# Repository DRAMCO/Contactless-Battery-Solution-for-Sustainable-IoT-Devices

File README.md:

# Contactless Battery Solution for Sustainable IoT Devices: Assessment of Environmental Impact

Supplementary material for "MDPI Electronics special issue Wireless Power Transfer Systems: Design and Implementation"

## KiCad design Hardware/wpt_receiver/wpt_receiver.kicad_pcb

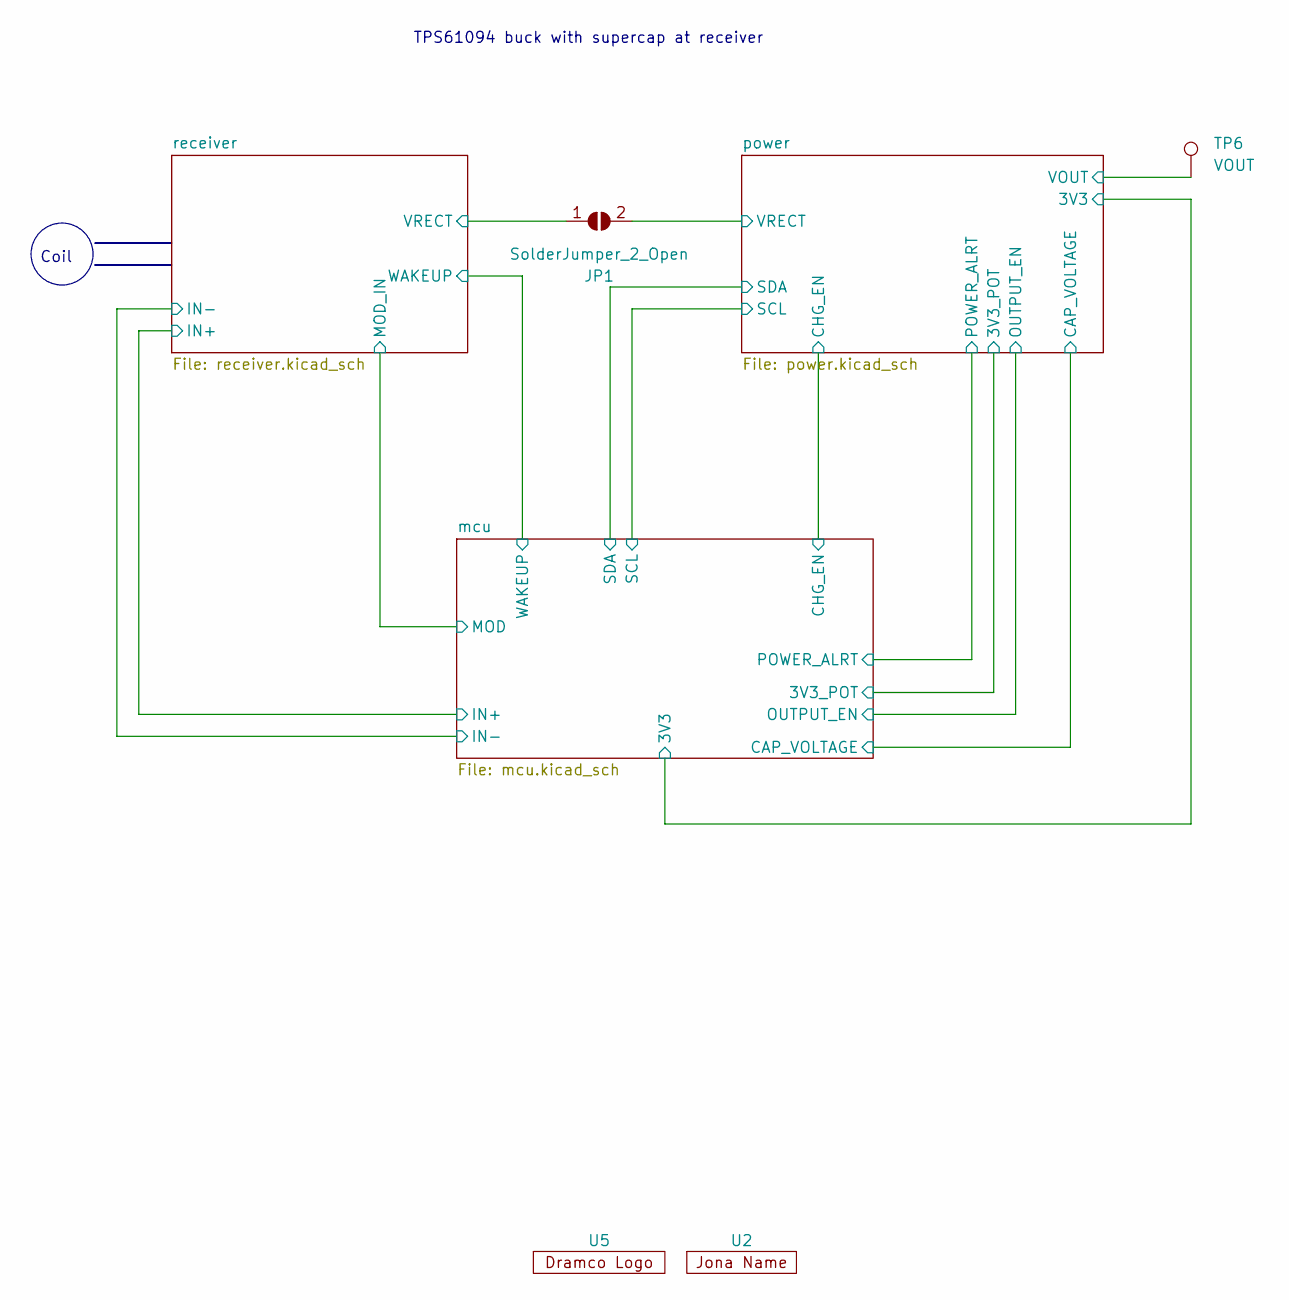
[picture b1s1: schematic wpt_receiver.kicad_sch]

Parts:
JP1: SolderJumper_2_Open; SolderJumper-2_P1.3mm_Open_RoundedPad1.0x1.5mm
TP6: VOUT; TestPoint_THTPad_2.5x2.5mm_Drill1.2mm
U2: Jona Name
U5: dramco_logo_small

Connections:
/power/VOUT: TP6.1; also elsewhere on the board
unnamed 32: JP1.1 (A); also elsewhere on the board
unnamed 33: JP1.2 (B); also elsewhere on the board

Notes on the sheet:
Coil
TPS61094 buck with supercap at receiver

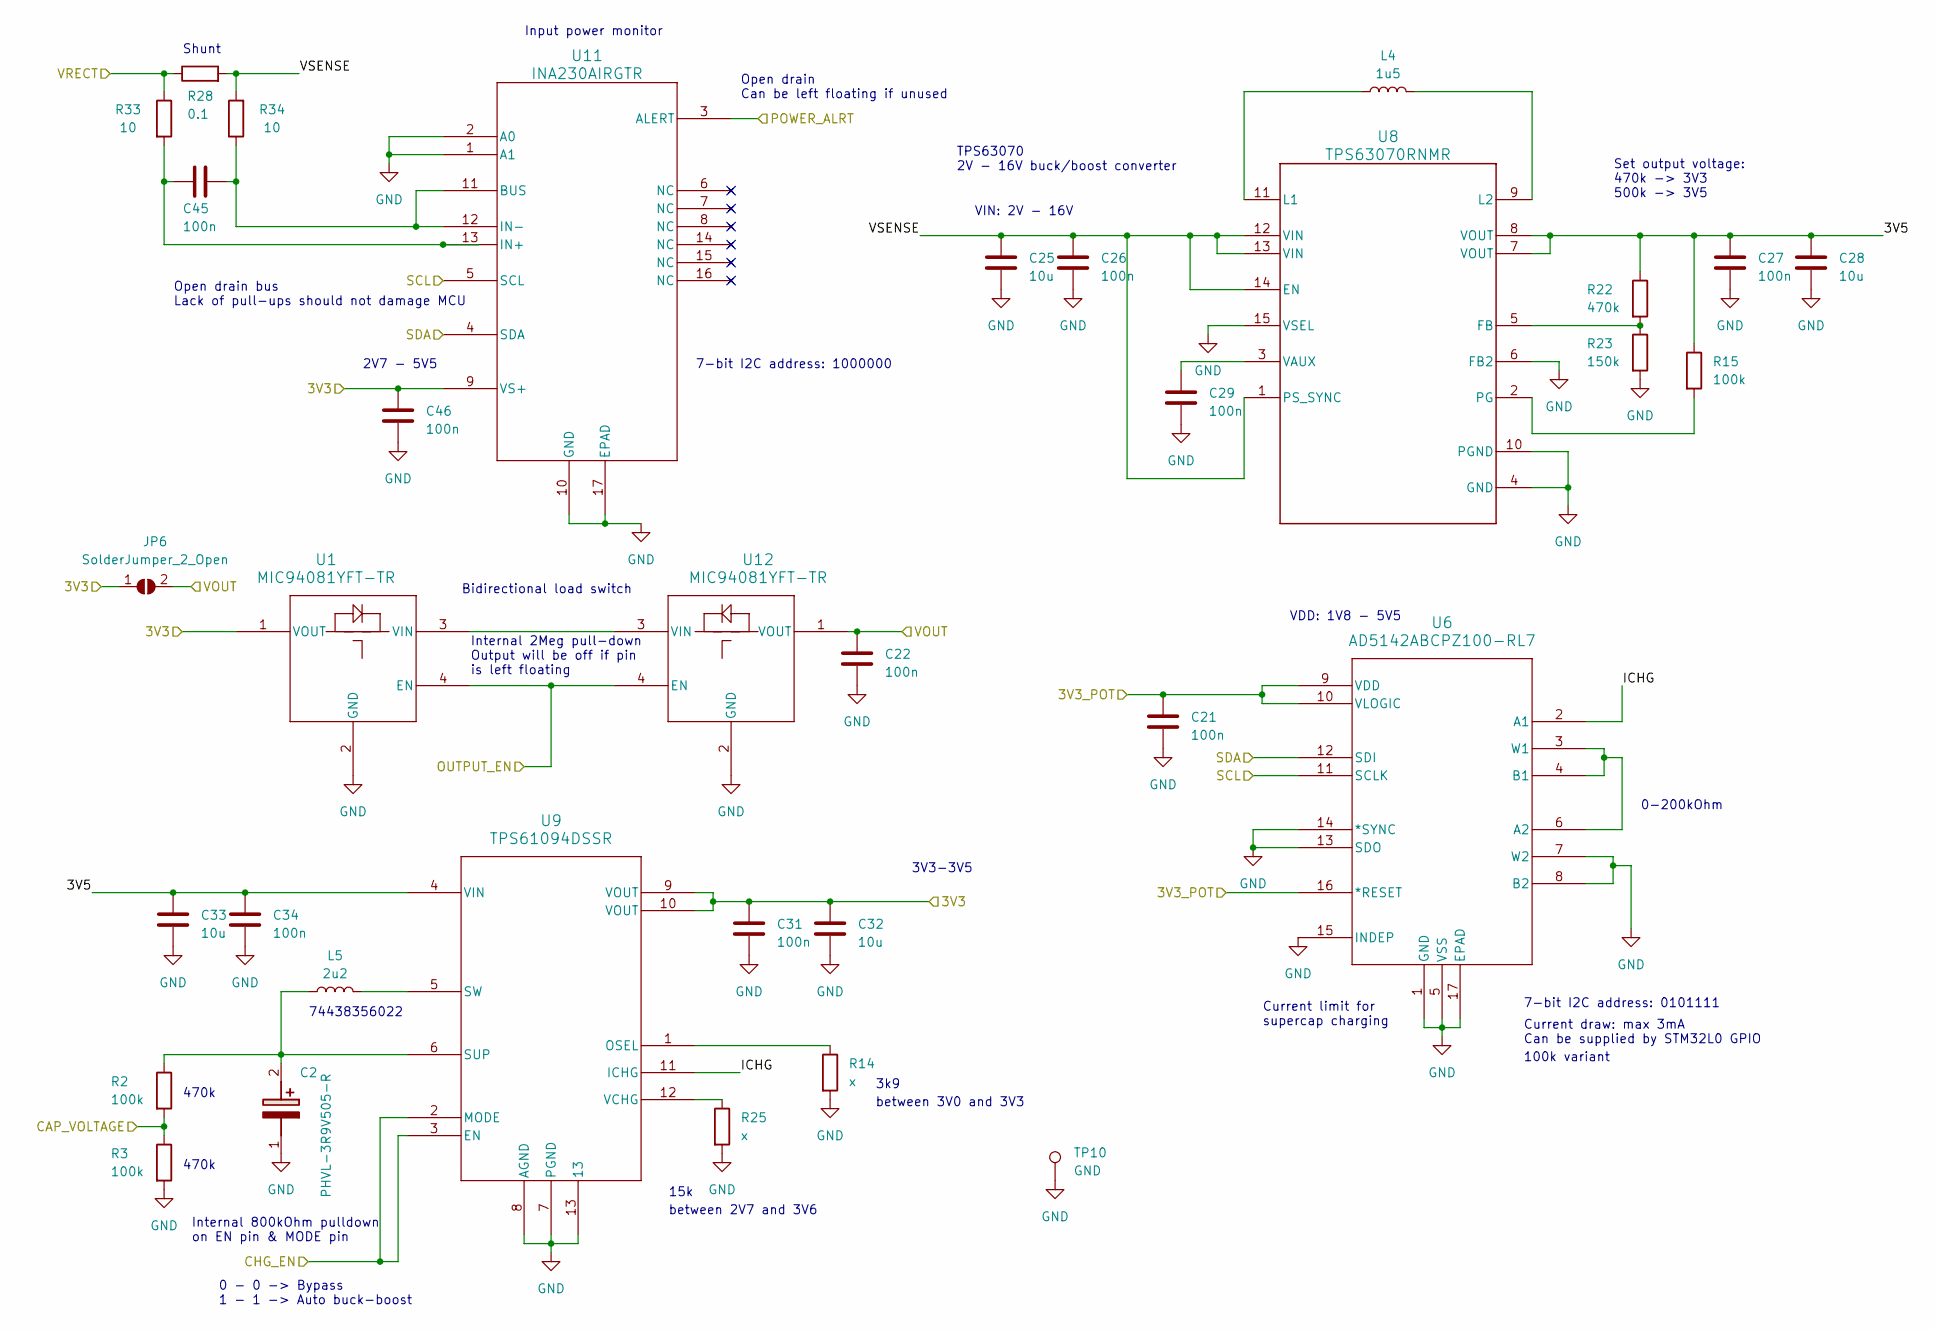
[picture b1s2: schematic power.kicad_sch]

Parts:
C2: PHVL-3R9V505-R; PHVL3R9V505R; Mouser Part Number 504-PHVL-3R9V505-R
C21, C22, C26, C27, C29, C31, C34, C45, C46: 100n; C_0603_1608Metric_Pad1.08x0.95mm_HandSolder
C25, C28, C32, C33: 10u; C_0603_1608Metric_Pad1.08x0.95mm_HandSolder
JP6: SolderJumper_2_Open; SolderJumper-2_P1.3mm_Open_RoundedPad1.0x1.5mm
L4: 1u5; L_Coilcraft_XxL4020
L5: 2u2; WE-MAPI_4020
R2, R3, R15: 100k; R_0603_1608Metric_Pad0.98x0.95mm_HandSolder
R14, R25: x; R_0603_1608Metric_Pad0.98x0.95mm_HandSolder
R22: 470k; R_0603_1608Metric_Pad0.98x0.95mm_HandSolder
R23: 150k; R_0603_1608Metric_Pad0.98x0.95mm_HandSolder
R28: 0.1; R_1206_3216Metric_Pad1.30x1.75mm_HandSolder
R33, R34: 10; R_0603_1608Metric_Pad0.98x0.95mm_HandSolder
TP10: GND; TestPoint_THTPad_2.5x2.5mm_Drill1.2mm
U1, U12: MIC94081YFT-TR; FTDFN085085-4LD-PL-1_MCH
U6: AD5142ABCPZ100-RL7; CP_16_22_ADI
U8: TPS63070RNMR; RNM0015A
U9: TPS61094DSSR; WSON_94DSSR_TEX
U11: INA230AIRGTR; RGT16_1P7X1P7

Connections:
/mcu/3V3: C31.1, C32.1, C46.1, JP6.1 (A), U1.1 (VOUT), U9.9 (VOUT), U9.10 (VOUT), U11.9 (VS+); also elsewhere on the board
/mcu/3V3_POT: C21.2, U6.9 (VDD), U6.10 (VLOGIC), U6.16 (*RESET); also elsewhere on the board
/mcu/CAP_VOLTAGE: R2.2, R3.1; also elsewhere on the board
/mcu/CHG_EN: U9.2 (MODE), U9.3 (EN); also elsewhere on the board
/mcu/OUTPUT_EN: U1.4 (EN), U12.4 (EN); also elsewhere on the board
/mcu/POWER_ALRT: U11.3 (ALERT); also elsewhere on the board
/mcu/SCL: U6.11 (SCLK), U11.5 (SCL); also elsewhere on the board
/mcu/SDA: U6.12 (SDI), U11.4 (SDA); also elsewhere on the board
/power/3V5: C27.1, C28.1, C33.1, C34.1, R15.1, R22.1, U8.7 (VOUT), U8.8 (VOUT), U9.4 (VIN)
/power/ICHG: U6.2 (A1), U9.11 (ICHG)
/power/VOUT: C22.1, JP6.2 (B), U12.1 (VOUT); also elsewhere on the board
/power/VRECT: R28.1, R33.1; also elsewhere on the board
/power/VSENSE: C25.1, C26.1, R28.2, R34.2, U8.1 (PS_SYNC), U8.12 (VIN), U8.13 (VIN), U8.14 (EN)
GND: C2.1 (-), C21.1, C22.2, C25.2, C26.2, C27.2, C28.2, C29.2, C31.2, C32.2, C33.2, C34.2, C46.2, R3.2, R14.2, R23.2, R25.2, TP10.1, U1.2 (GND), U6.1 (GND), U6.5 (VSS), U6.7 (W2), U6.8 (B2), U6.13 (SDO), U6.14 (*SYNC), U6.15 (INDEP), U6.17 (EPAD), U8.4 (GND), U8.6 (FB2), U8.10 (PGND), U8.15 (VSEL), U9.7 (PGND), U9.8 (AGND), U9.13, U11.1 (A1), U11.2 (A0), U11.10 (GND), U11.17 (EPAD), U12.2 (GND); also elsewhere on the board
unnamed: C2.2 (+), L5.1, R2.1, U9.6 (SUP)
unnamed: U1.3 (VIN), U12.3 (VIN)
unnamed: U6.3 (W1), U6.4 (B1), U6.6 (A2)
unnamed: R22.2, R23.1, U8.5 (FB)
unnamed: L4.1, U8.11 (L1)
unnamed: L4.2, U8.9 (L2)
unnamed: R15.2, U8.2 (PG)
unnamed: C29.1, U8.3 (VAUX)
unnamed: R14.1, U9.1 (OSEL)
unnamed: L5.2, U9.5 (SW)
unnamed: R25.1, U9.12 (VCHG)
unnamed: C45.1, R34.1, U11.11 (BUS), U11.12 (IN-)
unnamed: C45.2, R33.2, U11.13 (IN+)

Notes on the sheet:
7-bit I2C address: 0101111
between 2V7 and 3V6
0-200kOhm
15k
Internal 2Meg pull-down Output will be off if pin is left floating
3k9
Bidirectional load switch
Current draw: max 3mA Can be supplied by STM32L0 GPIO
VIN: 2V - 16V
between 3V0 and 3V3
Input power monitor
Set output voltage: 470k -> 3V3 500k -> 3V5
Open drain Can be left floating if unused
470k
Internal 800kOhm pulldown on EN pin & MODE pin
74438356022
Shunt
TPS63070 2V - 16V buck/boost converter
VDD: 1V8 - 5V5
Current limit for supercap charging
Open drain bus Lack of pull-ups should not damage MCU
0 - 0 -> Bypass 1 - 1 -> Auto buck-boost
2V7 - 5V5
3V3-3V5
100k variant
7-bit I2C address: 1000000

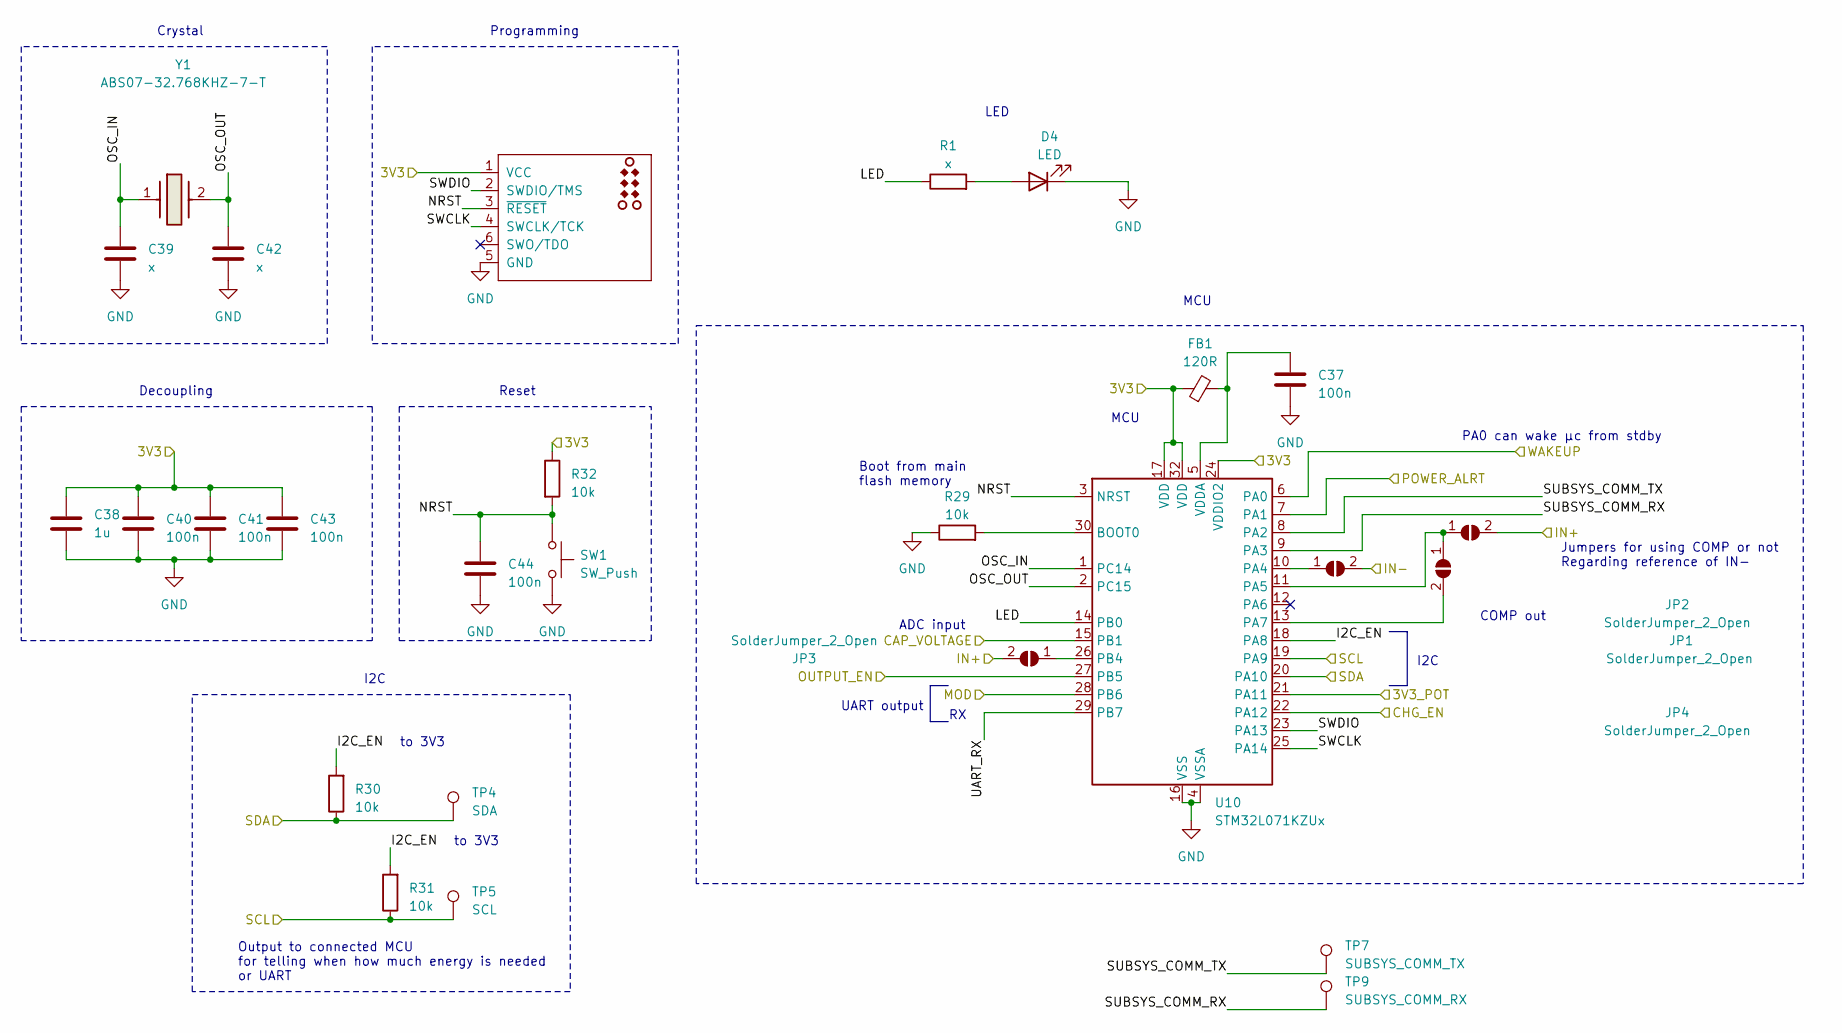
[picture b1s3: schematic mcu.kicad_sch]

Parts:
C37, C40, C41, C43, C44: 100n; C_0603_1608Metric_Pad1.08x0.95mm_HandSolder
C38: 1u; C_0603_1608Metric_Pad1.08x0.95mm_HandSolder
C39, C42: x; C_0603_1608Metric_Pad1.08x0.95mm_HandSolder
D4: LED; LED_0805_2012Metric_Pad1.15x1.40mm_HandSolder
FB1: 120R; C_0603_1608Metric_Pad1.08x0.95mm_HandSolder
J1: TC2030_SWD-MCP-NL; Tag-Connect_TC2030-IDC-NL_2x03_P1.27mm_Vertical
JP1, JP2, JP3, JP4: SolderJumper_2_Open; SolderJumper-2_P1.3mm_Open_RoundedPad1.0x1.5mm
R1: x; R_0603_1608Metric_Pad0.98x0.95mm_HandSolder
R29, R30, R31, R32: 10k; R_0603_1608Metric_Pad0.98x0.95mm_HandSolder
SW1: SW_Push; SW_Push_1P1T_NO_CK_KMR2
TP4: SDA; TestPoint_THTPad_2.5x2.5mm_Drill1.2mm
TP5: SCL; TestPoint_THTPad_2.5x2.5mm_Drill1.2mm
TP7: SUBSYS_COMM_TX; TestPoint_THTPad_2.5x2.5mm_Drill1.2mm
TP9: SUBSYS_COMM_RX; TestPoint_THTPad_2.5x2.5mm_Drill1.2mm
U10: STM32L071KZUx; QFN-32-1EP_5x5mm_P0.5mm_EP3.45x3.45mm
Y1: ABS07-32.768KHZ-7-T; ABS07; Mouser Part Number 815-ABS07-32.768K7T

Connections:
/mcu/3V3: C38.1, C40.1, C41.1, C43.1, FB1.1, J1.1 (VCC), R32.1, U10.17 (VDD), U10.24 (VDDIO2), U10.32 (VDD); also elsewhere on the board
/mcu/3V3_POT: U10.21 (PA11); also elsewhere on the board
/mcu/CAP_VOLTAGE: U10.15 (PB1); also elsewhere on the board
/mcu/CHG_EN: U10.22 (PA12); also elsewhere on the board
/mcu/I2C_EN: R30.2, R31.2, U10.18 (PA8)
/mcu/IN+: JP2.2 (B), JP3.2 (B); also elsewhere on the board
/mcu/LED: R1.1, U10.14 (PB0)
/mcu/MOD: U10.28 (PB6); also elsewhere on the board
/mcu/NRST: C44.1, J1.3 (~RESET), R32.2, SW1.1, U10.3 (NRST)
/mcu/OSC_IN: C39.1, U10.1 (PC14), Y1.1
/mcu/OSC_OUT: C42.1, U10.2 (PC15), Y1.2
/mcu/OUTPUT_EN: U10.27 (PB5); also elsewhere on the board
/mcu/POWER_ALRT: U10.7 (PA1); also elsewhere on the board
/mcu/SCL: R31.1, TP5.1, U10.19 (PA9); also elsewhere on the board
/mcu/SDA: R30.1, TP4.1, U10.20 (PA10); also elsewhere on the board
/mcu/SUBSYS_COMM_RX: TP9.1, U10.9 (PA3)
/mcu/SUBSYS_COMM_TX: TP7.1, U10.8 (PA2)
/mcu/SWCLK: J1.4 (SWCLK/TCK), U10.25 (PA14)
/mcu/SWDIO: J1.2 (SWDIO/TMS), U10.23 (PA13)
/mcu/UART_RX: U10.29 (PB7)
/mcu/WAKEUP: U10.6 (PA0); also elsewhere on the board
/receiver/COIL-: JP4.2 (B); also elsewhere on the board
GND: C37.2, C38.2, C39.2, C40.2, C41.2, C42.2, C43.2, C44.2, D4.1 (K), J1.5 (GND), R29.1, SW1.2, U10.4 (VSSA), U10.16 (VSS), U10.31 (VSS), U10.33 (VSS); also elsewhere on the board
unnamed: D4.2 (A), R1.2
unnamed: JP1.1 (A), JP2.1 (A), U10.11 (PA5)
unnamed: JP1.2 (B), U10.13 (PA7)
unnamed: JP3.1 (A), U10.26 (PB4)
unnamed: JP4.1 (A), U10.10 (PA4)
unnamed: R29.2, U10.30 (BOOT0)
unnamed: C37.1, FB1.2, U10.5 (VDDA)

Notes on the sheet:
I2C
Crystal
MCU
PA0 can wake µc from stdby
ADC input
Decoupling
Programming
Jumpers for using COMP or not Regarding reference of IN-
to 3V3
Reset
Boot from main flash memory
Output to connected MCU for telling when how much energy is needed or UART
LED
COMP out
UART output

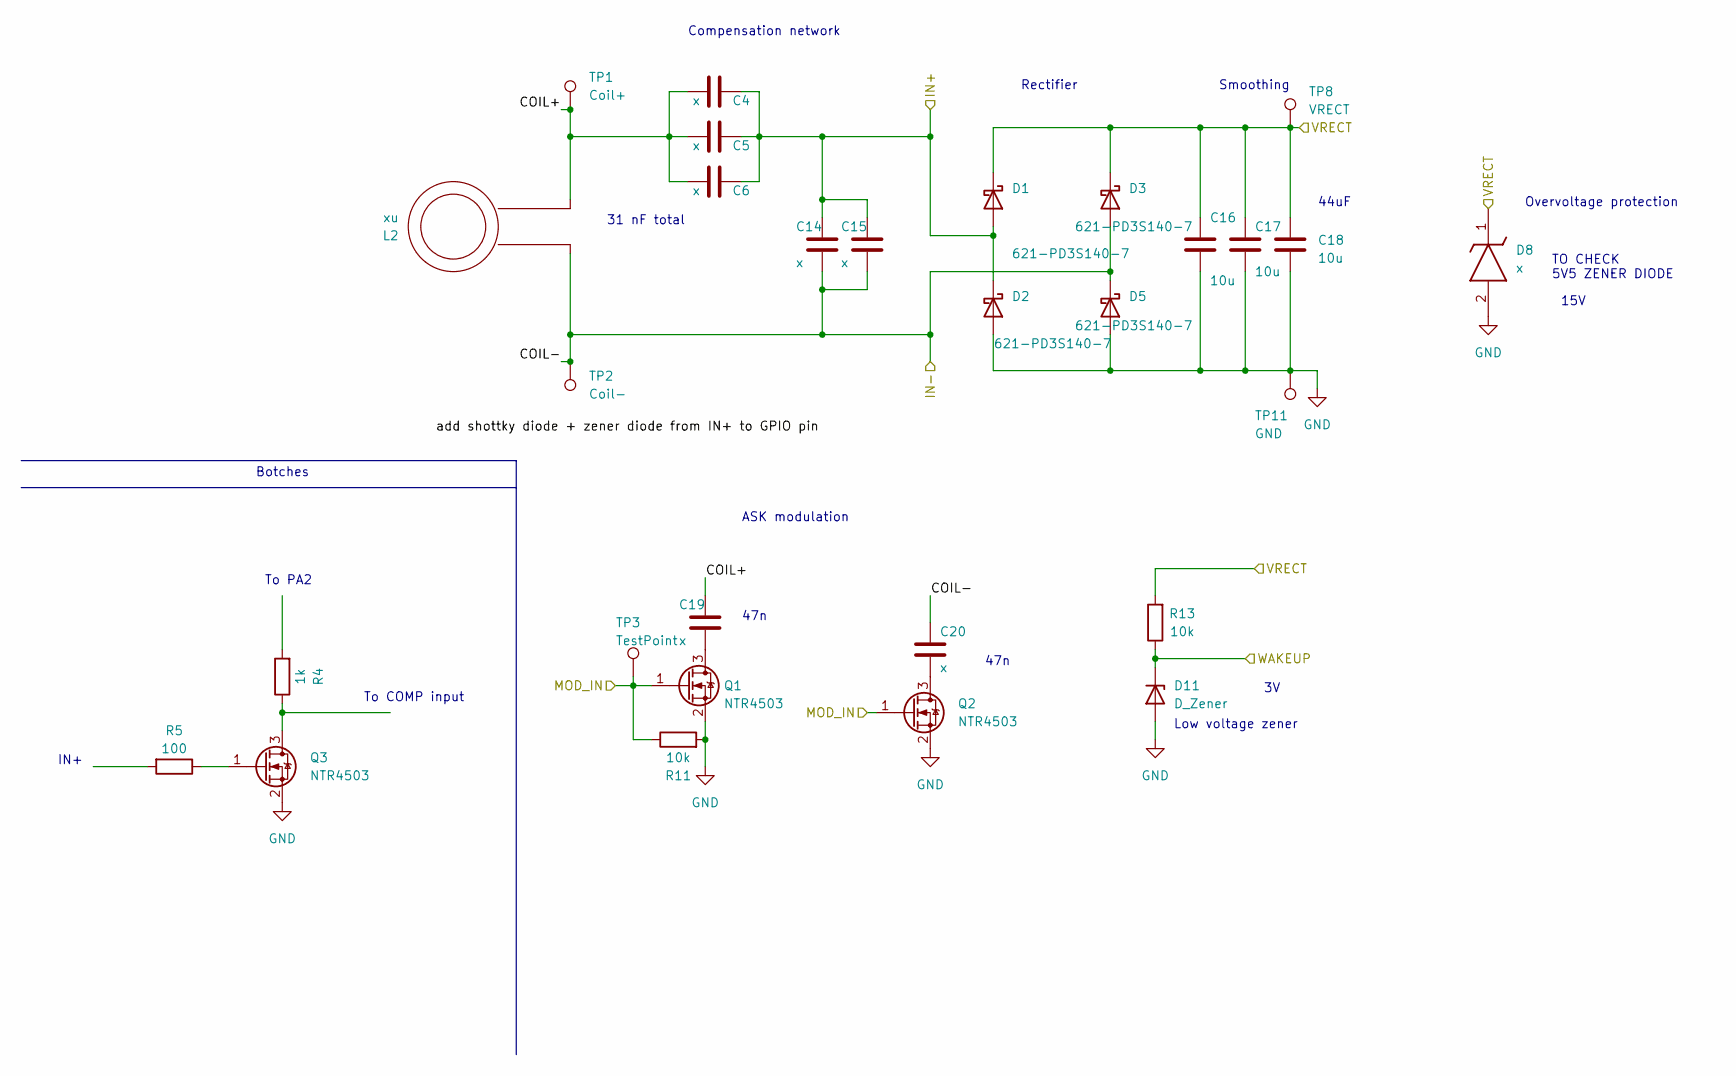
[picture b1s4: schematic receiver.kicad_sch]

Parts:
C4, C5, C6, C14, C15: x; C_0805_2012Metric_Pad1.18x1.45mm_HandSolder
C16, C17, C18: 10u; C_0603_1608Metric_Pad1.08x0.95mm_HandSolder
C19, C20: x; C_0603_1608Metric_Pad1.08x0.95mm_HandSolder
D1, D2, D3, D5: 621-PD3S140-7; D_SOD-323_HandSoldering
D8: x; D_SOD-323_HandSoldering; Mouser Part Number 621-D24V0S1U2TQ-7
D11: D_Zener; D_SOD-523
L2: xu; Wurth Coil Connector
Q1, Q2, Q3: NTR4503; SOT-23
R4: 1k; R_0603_1608Metric_Pad0.98x0.95mm_HandSolder
R5: 100; R_0603_1608Metric_Pad0.98x0.95mm_HandSolder
R11, R13: 10k; R_0603_1608Metric_Pad0.98x0.95mm_HandSolder
TP1: Coil+; TestPoint_THTPad_2.5x2.5mm_Drill1.2mm
TP2: Coil-; TestPoint_THTPad_2.5x2.5mm_Drill1.2mm
TP3: TestPoint; TestPoint_Pad_2.5x2.5mm
TP8: VRECT; TestPoint_THTPad_2.5x2.5mm_Drill1.2mm
TP11: GND; TestPoint_THTPad_2.5x2.5mm_Drill1.2mm

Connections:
/mcu/IN+: C4.2, C5.2, C6.2, C14.1, C15.1, D1.2 (A), D2.1 (K); also elsewhere on the board
/mcu/MOD: Q1.1 (G), Q2.1 (G), R11.1, TP3.1; also elsewhere on the board
/mcu/WAKEUP: D11.1 (K), R13.1; also elsewhere on the board
/receiver/COIL+: C4.1, C5.1, C6.1, C19.1, L2.2, TP1.1
/receiver/COIL-: C14.2, C15.2, C20.1, D3.2 (A), D5.1 (K), L2.1, TP2.1; also elsewhere on the board
/receiver/VRECT: C16.1, C17.1, C18.1, D1.1 (K), D3.1 (K), D8.1 (K), R13.2, TP8.1; also elsewhere on the board
GND: C16.2, C17.2, C18.2, D2.2 (A), D5.2 (A), D8.2 (A), D11.2 (A), Q1.2 (S), Q2.2 (S), Q3.2 (S), R11.2, TP11.1; also elsewhere on the board
unnamed: C19.2, Q1.3 (D)
unnamed: C20.2, Q2.3 (D)
unnamed: Q3.1 (G), R5.1
unnamed: Q3.3 (D), R4.1

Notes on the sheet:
Botches
47n
31 nF total
To COMP input
Low voltage zener
ASK modulation
IN+
Overvoltage protection
Rectifier
Compensation network
To PA2
15V
44uF
Smoothing
TO CHECK 5V5 ZENER DIODE

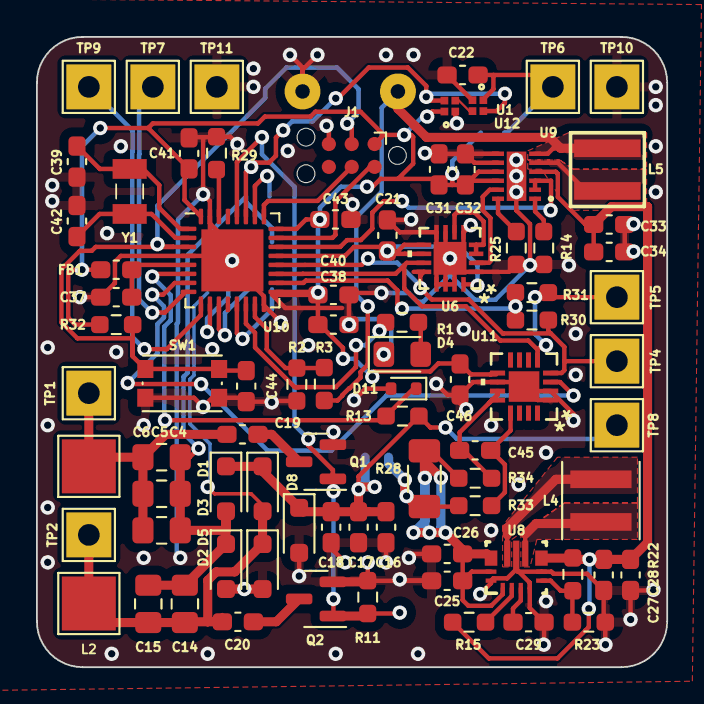
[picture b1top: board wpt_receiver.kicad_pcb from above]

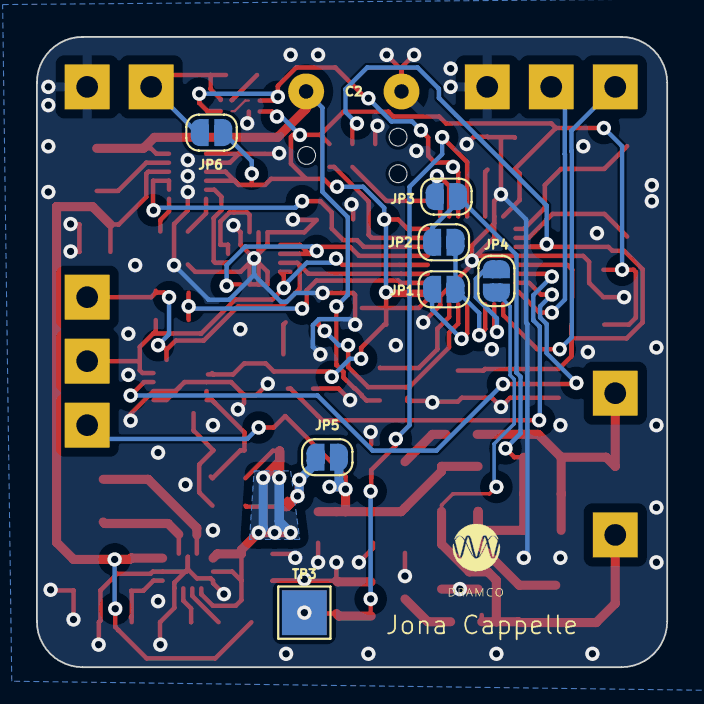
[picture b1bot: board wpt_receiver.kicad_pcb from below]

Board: 2 copper layers, 35.0 x 35.0 mm, 91 parts (9 on the bottom side), 51 nets.

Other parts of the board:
JP5: SolderJumper_2_Open; SolderJumper-2_P1.3mm_Open_RoundedPad1.0x1.5mm
U4: dramco_logo_small

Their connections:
/power/VRECT: JP5.2 (B); also elsewhere on the board
/receiver/VRECT: JP5.1 (A); also elsewhere on the board

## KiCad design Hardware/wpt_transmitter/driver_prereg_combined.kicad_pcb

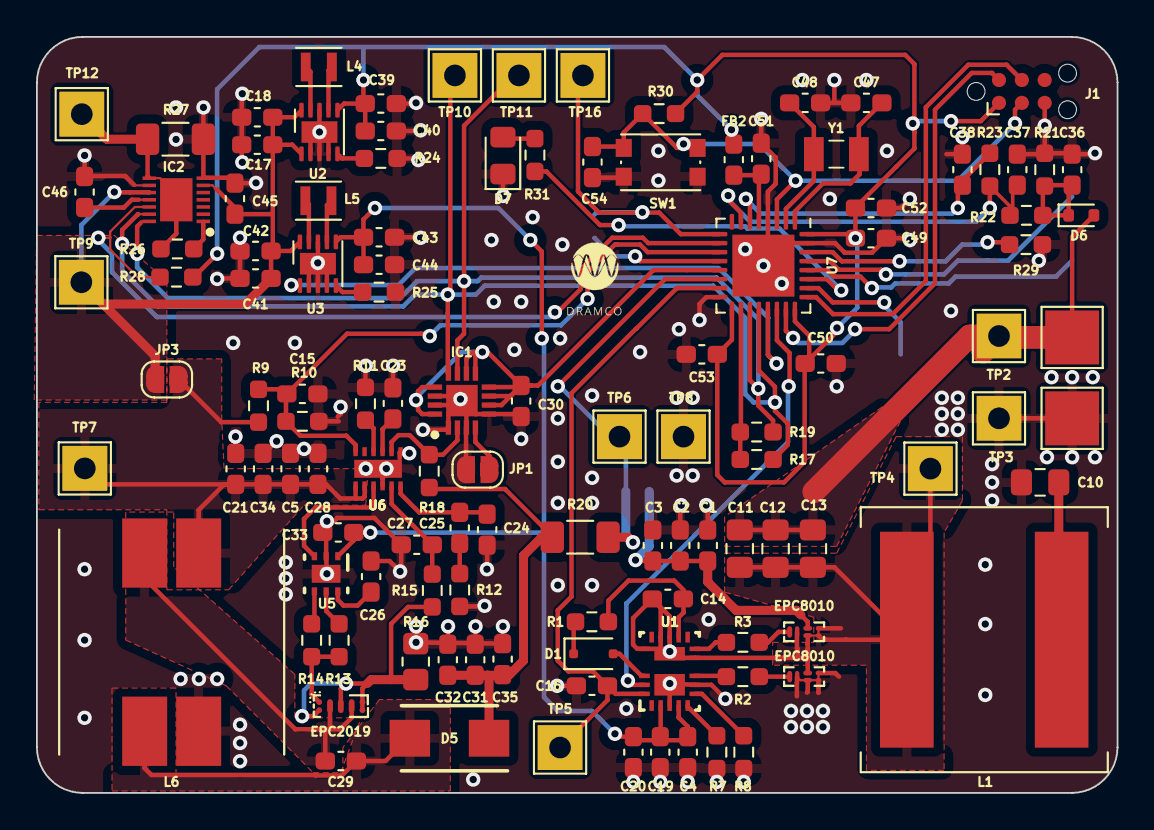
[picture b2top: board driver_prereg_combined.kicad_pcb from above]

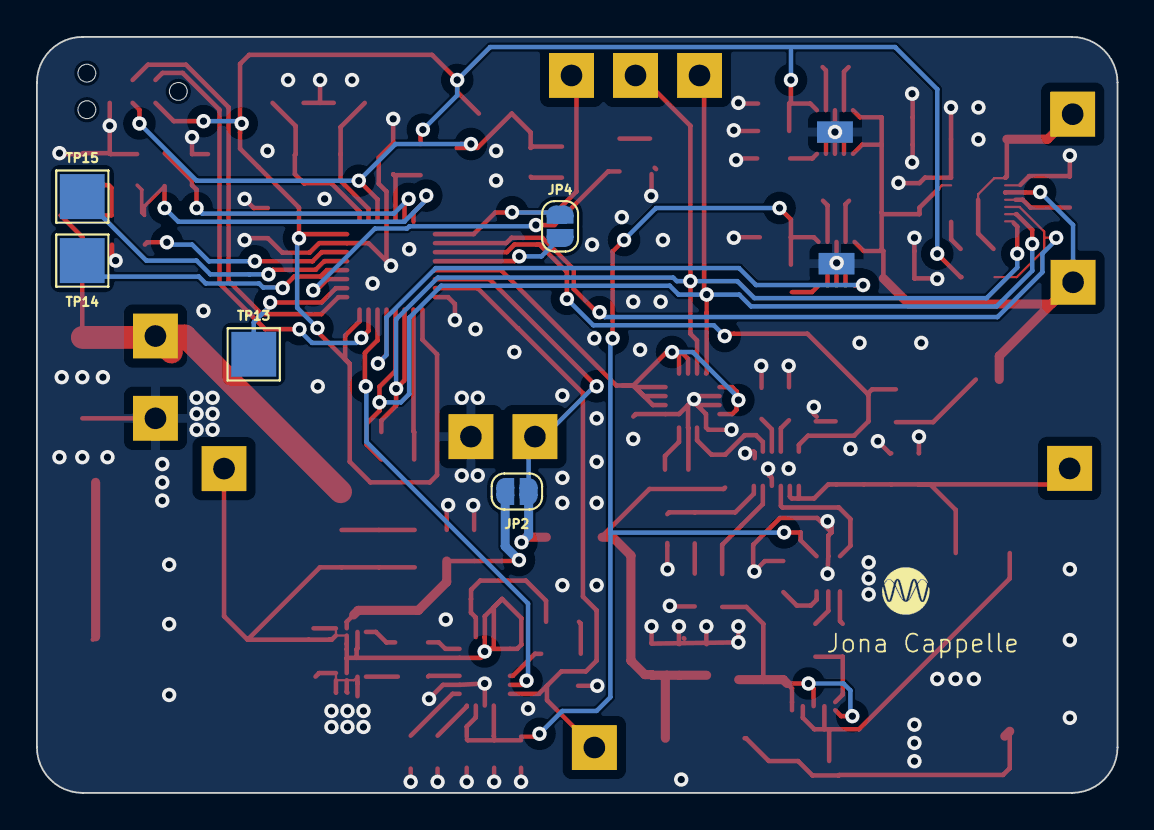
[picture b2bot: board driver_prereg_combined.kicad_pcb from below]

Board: 2 copper layers, 60.0 x 42.0 mm, 123 parts (7 on the bottom side), 70 nets.

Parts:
C1, C4, C14, C18, C20, C21, C26, C30, C31, C33, C40, C42, C43, C45, C49, C50, C51, C53, C54: 100n; C_0603_1608Metric_Pad1.08x0.95mm_HandSolder
C2, C3, C5, C17, C19, C32, C34, C35, C39, C41, C44: 10u; C_0603_1608Metric_Pad1.08x0.95mm_HandSolder
C10: 1u 50V; C_0805_2012Metric_Pad1.18x1.45mm_HandSolder
C11, C12, C13: 10n; C_0805_2012Metric_Pad1.18x1.45mm_HandSolder
C15, C27, C29: 100p; C_0603_1608Metric_Pad1.08x0.95mm_HandSolder
C16: 22p; C_0603_1608Metric_Pad1.08x0.95mm_HandSolder
C23: 220n; C_0603_1608Metric_Pad1.08x0.95mm_HandSolder
C24: 180p; C_0603_1608Metric_Pad1.08x0.95mm_HandSolder
C25: 680p; C_0603_1608Metric_Pad1.08x0.95mm_HandSolder
C28, C52: 1u; C_0603_1608Metric_Pad1.08x0.95mm_HandSolder
C36, C37, C38, C47, C48: x; C_0603_1608Metric_Pad1.08x0.95mm_HandSolder
C46: 470n; C_0603_1608Metric_Pad1.08x0.95mm_HandSolder
D1: BAT46WJ,115; D_SOD-323F
D5: 755-RB068LB100TBR1; RB068LB100TBR1
D6: 1N4148WS; D_SOD-523
D7: LED; LED_0805_2012Metric_Pad1.15x1.40mm_HandSolder
FB2: 120R; C_0603_1608Metric_Pad1.08x0.95mm_HandSolder
IC1: AD5121BCPZ100-RL7
IC2: MAX17260SETD+; SON40P300X300X80-15N
J1: TC2030_SWD-MCP-NL; Tag-Connect_TC2030-IDC-NL_2x03_P1.27mm_Vertical
JP1, JP2, JP3, JP4: SolderJumper_2_Open; SolderJumper-2_P1.3mm_Open_RoundedPad1.0x1.5mm
L1: x; L_Coilcraft_XAL1350-XXX
L2: 6.8u; Wurth Coil Connector
L4, L5: 2u2; L_Murata_DFE201610P
L6: 744870006; WE-DD_12XX_CROSSED12
Q1, Q2: EPC8010; EPC8000
Q4: EPC2019; EPC2X200M
R1, R13, R14, R15: 100; R_0603_1608Metric_Pad0.98x0.95mm_HandSolder
R2, R3: 0; R_0603_1608Metric_Pad0.98x0.95mm_HandSolder
R7, R8, R10, R17, R19, R28, R29, R30: 10k; R_0603_1608Metric_Pad0.98x0.95mm_HandSolder
R9: 15k; R_0603_1608Metric_Pad0.98x0.95mm_HandSolder
R11: 9.31k; R_0603_1608Metric_Pad0.98x0.95mm_HandSolder
R12: 64.9k; R_0603_1608Metric_Pad0.98x0.95mm_HandSolder
R16: 5.149m; R_0805_2012Metric_Pad1.20x1.40mm_HandSolder
R18: 500k; R_0603_1608Metric_Pad0.98x0.95mm_HandSolder
R20, R27: 20m; R_1206_3216Metric_Pad1.30x1.75mm_HandSolder
R21, R22, R23, R31: x; R_0603_1608Metric_Pad0.98x0.95mm_HandSolder
R24: 16k2; R_0603_1608Metric_Pad0.98x0.95mm_HandSolder
R25: 36k5; R_0603_1608Metric_Pad0.98x0.95mm_HandSolder
R26: 10k NTC; R_0603_1608Metric_Pad0.98x0.95mm_HandSolder
SW1: SW_Push; SW_Push_1P1T_NO_CK_KMR2
TP2: Coil+; TestPoint_THTPad_2.5x2.5mm_Drill1.2mm
TP3: Coil-; TestPoint_THTPad_2.5x2.5mm_Drill1.2mm
TP4: SW; TestPoint_THTPad_2.5x2.5mm_Drill1.2mm
TP5: CLK; TestPoint_THTPad_2.5x2.5mm_Drill1.2mm
TP6: Vout; TestPoint_THTPad_2.5x2.5mm_Drill1.2mm
TP7: Vin; TestPoint_THTPad_2.5x2.5mm_Drill1.2mm
TP8: GND; TestPoint_THTPad_2.5x2.5mm_Drill1.2mm
TP9: Vbat+; TestPoint_THTPad_2.5x2.5mm_Drill1.2mm
TP10: SDA; TestPoint_THTPad_2.5x2.5mm_Drill1.2mm
TP11: SCL; TestPoint_THTPad_2.5x2.5mm_Drill1.2mm
TP12: Vbat-; TestPoint_THTPad_2.5x2.5mm_Drill1.2mm
TP13: TIM22; TestPoint_Pad_2.5x2.5mm
TP14: USART_TX; TestPoint_Pad_2.5x2.5mm
TP15: USART_RX; TestPoint_Pad_2.5x2.5mm
TP16: LPUART_RX; TestPoint_THTPad_2.5x2.5mm_Drill1.2mm
U1: LMG1210RVRR; LMG1210
U2, U3: TPS63900; WSON-10-1EP_2.5x2.5mm_P0.5mm_EP1.2x2mm_ThermalVias
U4, U9: dramco_logo_small
U5: UCC27611DRVR; DRV0006A
U6: LM51561DSSR; DSS0012B
U7: STM32L071KZUx; QFN-32-1EP_5x5mm_P0.5mm_EP3.45x3.45mm
U8: Jona Name
Y1: ABS07-32.768KHZ-7-T; ABS07

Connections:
/ask_demod/COIL_IN: C11.2, C12.2, C13.2, D6.2 (A), L2.1, TP2.1
/ask_demod/COMP+: C37.1, R22.2, R23.1, U7.7 (PA1)
/ask_demod/COMP-: C38.1, R23.2, U7.6 (PA0)
/batt_mgmt/3V3: C39.1, C40.1, C49.1, C50.1, C52.1, C53.1, FB2.1, J1.1 (VCC), R28.1, R30.1, U2.6 (VOUT), U7.17 (VDD), U7.24 (VDDIO2), U7.32 (VDD)
/batt_mgmt/5V: C4.2, C19.1, C20.1, C33.2, C43.1, C44.1, U1.2 (VIN), U1.4 (VCC), U3.6 (VOUT), U5.1 (VDD)
/batt_mgmt/5V_EN: U3.1 (EN), U7.21 (PA11)
/batt_mgmt/ALRT: IC2.12 (ALRT), R28.2, U7.10 (PA4)
/batt_mgmt/SCL: IC1.11 (SCLK/SCL), IC2.14 (SCL), R19.1, TP11.1, U7.19 (PA9)
/batt_mgmt/SDA: IC1.12 (SDI/SDA), IC2.13 (SDA), R17.1, TP10.1, U7.20 (PA10)
/batt_mgmt/V_BAT: C17.1, C18.1, C41.1, C42.1, C45.1, IC2.6 (BATT), IC2.10 (CSPH), JP3.1 (A), TP9.1, U2.1 (EN), U2.10 (VIN), U3.10 (VIN)
/driver/CLK: C16.2, TP5.1, U1.19 (PWM_LI), U7.15 (PB1)
/driver/ENABLE: U1.18 (HI_EN), U7.22 (PA12)
/driver/HB: C14.2, R1.1, U1.12 (HB)
/driver/HS: C11.1, C12.1, C13.1, C14.1, L1.1, Q1.2 (SG), Q1.3 (SP1), Q1.5 (SP2), Q1.6 (Sub), Q2.4 (D), TP4.1, U1.9 (HS), U1.13 (HS), U1.14 (HS), U1.16 (HS), U1.21 (HS_DAP)
/driver/LO: R2.1, U1.8 (LO)
/driver/V_SUPPLY: C1.2, C2.2, C3.2, JP2.2 (B), Q1.4 (D)
/mcu/I2C_EN: R17.2, R19.2, U7.18 (PA8)
/mcu/LED: R31.1, U7.27 (PB5)
/mcu/LPUART_RX: JP4.1 (A), TP16.1, U7.9 (PA3)
/mcu/NRST: C54.1, J1.3 (~RESET), R30.2, SW1.1, U7.3 (NRST)
/mcu/OSC_IN: C47.1, U7.1 (PC14), Y1.1
/mcu/OSC_OUT: C48.1, U7.2 (PC15), Y1.2
/mcu/POT_EN: C30.2, IC1.6 (~SYNC/ADDR0), IC1.7 (~RESET), IC1.8 (DIS), IC1.9 (VDD), IC1.10 (VLOGIC), IC1.13 (~WP), IC1.16 (~LRDAC), U7.13 (PA7)
/mcu/SEPIC_EN: C15.2, R9.1, R10.2, U6.12 (UVLO_SYNC_EN), U7.11 (PA5)
/mcu/SWCLK: J1.4 (SWCLK/TCK), U7.25 (PA14)
/mcu/SWDIO: J1.2 (SWDIO/TMS), U7.23 (PA13)
/mcu/TIM22_CH1_DEBUG: TP13.1, U7.26 (PB4)
/mcu/USART1_RX: TP15.1, U7.29 (PB7)
/mcu/USART1_TX: TP14.1, U7.28 (PB6)
/mcu/V_SEPIC: JP2.1 (A), R20.2, TP6.1, U7.14 (PB0)
/sepic/CS: Q4.2 (S3), Q4.4 (S1), Q4.6 (S2), Q4.7 (Sub), R15.1, R16.2
/sepic/FB: IC1.2 (A), R18.1, U6.8 (FB)
/sepic/GATE: U5.3 (IN+), U6.3 (GATE)
/sepic/GaN FET Vsw: C29.2, L6.2 (1), Q4.3 (D1), Q4.5 (D2)
/sepic/VIN: C5.2, C21.2, C28.2, C34.2, JP3.2 (B), L6.1 (3), R9.2, TP7.1, U6.1 (BIAS), U6.2 (VCC)
/sepic/VOUT1: C31.2, C32.2, C35.2, D5.1 (K), R18.2, R20.1
GND: C1.1, C2.1, C3.1, C4.1, C5.1, C10.2, C15.1, C16.1, C17.2, C18.2, C19.2, C20.2, C21.1, C23.1, C24.1, C26.1, C27.1, C28.1, C30.1, C31.1, C32.1, C33.1, C34.1, C35.1, C36.2, C37.2, C38.2, C39.2, C40.2, C41.2, C42.2, C43.2, C44.2, C45.2, C46.2, C47.2, C48.2, C49.2, C50.2, C51.2, C52.2, C53.2, C54.2, D7.1 (K), IC1.1 (GND), IC1.3 (W), IC1.5 (VSS_1), IC1.14 (SDO/ADDR1), IC1.15 (INDEP), IC1.17 (VSS_2), IC2.7 (CSN), IC2.9 (CSPL), J1.5 (GND), JP1.1 (A), L2.2, L6.4 (2), Q2.2 (SG), Q2.3 (SP1), Q2.5 (SP2), Q2.6 (Sub), R7.1, R8.1, R10.1, R11.1, R12.1, R16.1, R21.2, R24.2, R25.2, R27.2, R29.1, SW1.2, TP3.1, TP8.1, U1.3 (VSS), U1.7 (VSS), U1.20 (LS_DAP), U2.2 (SEL), U2.3 (CFG1), U2.4 (CFG2), U2.8 (GND), U2.11 (GND), U3.2 (SEL), U3.3 (CFG1), U3.4 (CFG2), U3.8 (GND), U3.11 (GND), U5.2 (IN-), U5.7 (PAD), U6.4 (GND), U6.7 (DITHOFF), U6.13 (EP), U7.4 (VSSA), U7.16 (VSS), U7.31 (VSS), U7.33 (VSS)
unnamed: C10.1, L1.2
unnamed: C25.1, R12.2
unnamed: D1.2 (A), U1.17 (BST)
unnamed: D1.1 (K), R1.2
unnamed: C29.1, D5.2 (A), L6.3 (4)
unnamed: C36.1, D6.1 (K), R21.1, R22.1
unnamed: D7.2 (A), R31.2
unnamed: IC1.4 (B), JP1.2 (B)
unnamed: IC2.8 (GND), IC2.15 (EP), R26.2, R27.1, TP12.1
unnamed: C46.1, IC2.11 (REG)
unnamed: IC2.1 (TH), R26.1
unnamed: JP4.2 (B), U7.12 (PA6)
unnamed: Q1.1 (G), R3.2
unnamed: Q2.1 (G), R2.2
unnamed: Q4.1 (G), R13.1, R14.1
unnamed: R7.2, U1.5 (DHL)
unnamed: R8.2, U1.6 (DLH)
unnamed: R3.1, U1.10 (HO)
unnamed: R24.1, U2.5 (CFG3)
unnamed: L4.2, U2.9 (LX1)
unnamed: L4.1, U2.7 (LX2)
unnamed: R25.1, U3.5 (CFG3)
unnamed: L5.2, U3.9 (LX1)
unnamed: L5.1, U3.7 (LX2)
unnamed: R13.2, U5.5 (OUTH)
unnamed: R14.2, U5.4 (OUTL)
unnamed: C26.2, U5.6 (VREF)
unnamed: C24.2, C25.2, U6.6 (COMP)
unnamed: C27.2, R15.2, U6.5 (CS)
unnamed: R11.2, U6.10 (RT)
unnamed: C23.2, U6.9 (SS)
unnamed: R29.2, U7.30 (BOOT0)
unnamed: C51.1, FB2.2, U7.5 (VDDA)

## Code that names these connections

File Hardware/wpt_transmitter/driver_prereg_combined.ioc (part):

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Mcu.Name=STM32L071K(B-Z)Ux
Mcu.Package=UFQFPN32
Mcu.UserName=STM32L071KZUx
PA0.Mode=INM
PA0.Signal=COMP1_INM
PA1.Mode=INP
PA1.Signal=COMP1_INP
PA10.Mode=I2C
PA10.Signal=I2C1_SDA
PA11.GPIOParameters=GPIO_Label
PA11.GPIO_Label=VDD_5V_EN
PA11.Signal=GPIO_Output
PA12.GPIOParameters=GPIO_Label
PA12.GPIO_Label=DRV_EN
PA12.Signal=GPIO_Output
PA13.Mode=Serial_Wire
PA13.Signal=SYS_SWDIO
PA14.Mode=Serial_Wire
PA14.Signal=SYS_SWCLK
PA2.Mode=Asynchronous
PA2.Signal=LPUART1_TX
PA3.GPIOParameters=GPIO_Label
PA3.GPIO_Label=ASK_in
PA3.Mode=Asynchronous
PA3.Signal=LPUART1_RX
PA4.GPIOParameters=GPIO_Label
PA4.GPIO_Label=BAT_ALRT
PA4.Signal=GPIO_Input
PA5.GPIOParameters=GPIO_Label
PA5.GPIO_Label=SEPIC_EN
PA5.Signal=GPIO_Output
PA6.Mode=ExternalOutput
PA6.Signal=COMP1_OUT
PA7.GPIOParameters=GPIO_Label
PA7.GPIO_Label=POT_EN
PA7.Signal=GPIO_Output
PA8.GPIOParameters=GPIO_Label
PA8.GPIO_Label=I2C_EN
PA8.Signal=GPIO_Input
PA9.Mode=I2C
PA9.Signal=I2C1_SCL
PB0.GPIOParameters=GPIO_Label
PB0.GPIO_Label=V_SEPIC
PB0.Mode=IN8
PB0.Signal=ADC_IN8
PB1.GPIOParameters=GPIO_Label
PB1.GPIO_Label=CLK_out
PB1.Signal=S_TIM3_CH4
PB4.Signal=S_TIM22_CH1
PB5.GPIOParameters=GPIO_Label
PB5.GPIO_Label=LED
PB5.Signal=GPIO_Output
PB6.Mode=Asynchronous
PB6.Signal=USART1_TX
PB7.Mode=Asynchronous
PB7.Signal=USART1_RX
PC14-OSC32_IN.Mode=LSE-External-Oscillator
PC14-OSC32_IN.Signal=RCC_OSC32_IN
PC15-OSC32_OUT.Mode=LSE-External-Oscillator
PC15-OSC32_OUT.Signal=RCC_OSC32_OUT
RCC.SYSCLKFreq_VALUE=32000000
RCC.SYSCLKSource=RCC_SYSCLKSOURCE_PLLCLK
board=custom

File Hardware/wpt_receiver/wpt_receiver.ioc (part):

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Mcu.Name=STM32L071K(B-Z)Ux
Mcu.Package=UFQFPN32
Mcu.UserName=STM32L071KZUx
PA1.GPIOParameters=GPIO_Label
PA1.GPIO_Label=POWER_ALRT
PA1.Signal=GPIO_Input
PA10.Mode=I2C
PA10.Signal=I2C1_SDA
PA11.GPIOParameters=GPIO_Label
PA11.GPIO_Label=POT_3V3
PA11.Signal=GPIO_Output
PA12.GPIOParameters=GPIO_PuPd,GPIO_Label,GPIO_ModeDefaultOutputPP
PA12.GPIO_Label=CHG_EN
PA12.GPIO_ModeDefaultOutputPP=GPIO_MODE_OUTPUT_PP
PA12.GPIO_PuPd=GPIO_NOPULL
PA12.Signal=GPIO_Output
PA13.Mode=Serial_Wire
PA13.Signal=SYS_SWDIO
PA14.Mode=Serial_Wire
PA14.Signal=SYS_SWCLK
PA2.Mode=Asynchronous
PA2.Signal=LPUART1_TX
PA3.Mode=Asynchronous
PA3.Signal=LPUART1_RX
PA4.Mode=INM
PA4.Signal=COMP2_INM
PA5.Signal=S_TIM2_CH1
PA7.Mode=ExternalOutput
PA7.Signal=COMP2_OUT
PA8.GPIOParameters=GPIO_Label
PA8.GPIO_Label=I2C_enable
PA8.Signal=GPIO_Output
PA9.Mode=I2C
PA9.Signal=I2C1_SCL
PB0.GPIOParameters=GPIO_Label
PB0.GPIO_Label=LED
PB0.Signal=GPIO_Output
PB1.GPIOParameters=GPIO_Label
PB1.GPIO_Label=RX_Voltage
PB1.Mode=IN9
PB1.Signal=ADC_IN9
PB4.Mode=INP
PB4.Signal=COMP2_INP
PB6.Mode=Asynchronous
PB6.Signal=USART1_TX
PB7.Mode=Asynchronous
PB7.Signal=USART1_RX
PC14-OSC32_IN.Mode=LSE-External-Oscillator
PC14-OSC32_IN.Signal=RCC_OSC32_IN
PC15-OSC32_OUT.Mode=LSE-External-Oscillator
PC15-OSC32_OUT.Signal=RCC_OSC32_OUT
RCC.SYSCLKFreq_VALUE=2097000
board=custom

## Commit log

2025-10-04 Paper supplementary material
2025-10-04 change extension
